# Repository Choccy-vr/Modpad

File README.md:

# Modpad
> An open-source, hot-swappable modular macro pad system with live browser-based key mapping.

Modpad combines hardware and software to create an adaptable modular macropad. Rather than locking users in a fixed, rigid layout, keyboard layout, or proprietary config software, Modpad allows users to magnetically hot-swap satellite modules into a main module and reconfigure key actions and layout all in real time.

Configurator URL: https://modpad.vercel.app/
Demo Video: https://youtu.be/VHo8qCPebk0

---
## Features
- **Dynamic Module Discovery:** Automatically identifies and polls attached satellite modules using i2c
- **Zero-Install Configurator:** Uses web serial to read active layouts, update bindings, and provide real-time input status all with a website.
- **Dynamic Remapping:** Keymaps are refreshed directly in the microcontroller's RAM; no need to restart every time.
- **Full HID & Consumer Control Support:** Emulates standard keyboard keystrokes, modifiers, and media controls (Volume, Play/Pause, Brightness).

## Modules
- **Macro:** The standard-sized macro pad. 6 completely remappable buttons.
- **Knobs:** 2 Rotary Encoders. Perfect for volume and brightness.
- More in the works

## Protocol
The web configurator and the main module communicate over USB serial (115200 baud) using newline-delimited JSON. Each message is a single JSON object ending in `\n`.

| Message | Direction | Description | Example |
|---|---|---|---|
| `get_layout` | Web -> Board | Requests the keymap of every module | `{"cmd":"get_layout"}` |
| `layout` | Board -> Web | Returns each module's keymap as a list of actions | `{"status":"layout","modules":{"Macro":[{"code":4,"mod":0,"consumer":false}, ...]}}` |
| `get_modules` | Web -> Board | Requests which modules are currently connected | `{"cmd":"get_modules"}` |
| `modules` | Board -> Web | Returns the connection state of each module | `{"status":"modules","modules":{"Macro":true,"Knobs":false}}` |
| `set_key` | Web -> Board | Rebinds one key or knob direction in RAM | `{"cmd":"set_key","module":"Macro","index":2,"code":4,"modifiers":0,"consumer":false}` |
| `ok` / `error` | Board -> Web | Reply to `set_key` | `{"status":"ok"}` / `{"status":"error","msg":"invalid_key_or_module"}` |
| `press` | Board -> Web | Sent whenever a button or knob is used | `{"status":"press","module":{"name":"Macro","index":2,"type":"button"}}` |
| `log` | Board -> Web | Debug message, so the serial stream stays pure JSON | `{"status":"log","msg":"..."}` |

### Fields
- `code`: HID keyboard usage ID, or a consumer usage ID when `consumer` is `true` (for example `0xE9` for Volume +).
- `modifiers` / `mod`: Modifier bitmask (`0x01` LCtrl, `0x02` LShift, `0x04` LAlt, `0x08` LGui, `0x10` RCtrl, `0x20` RShift, `0x40` RAlt, `0x80` RGui).
- `index`: Position in the module's keymap. It's the same index for `set_key` and `press`.

---

---
## Pictures
### Configurator

### Main Module
#### Schematic

#### PCB

#### PCB 3D model

#### CAD

### Macro Module
#### Schematic

#### PCB

#### PCB 3D model

#### CAD

### Knobs Module
#### Schematic

#### PCB

#### PCB 3D model

#### CAD

### Built

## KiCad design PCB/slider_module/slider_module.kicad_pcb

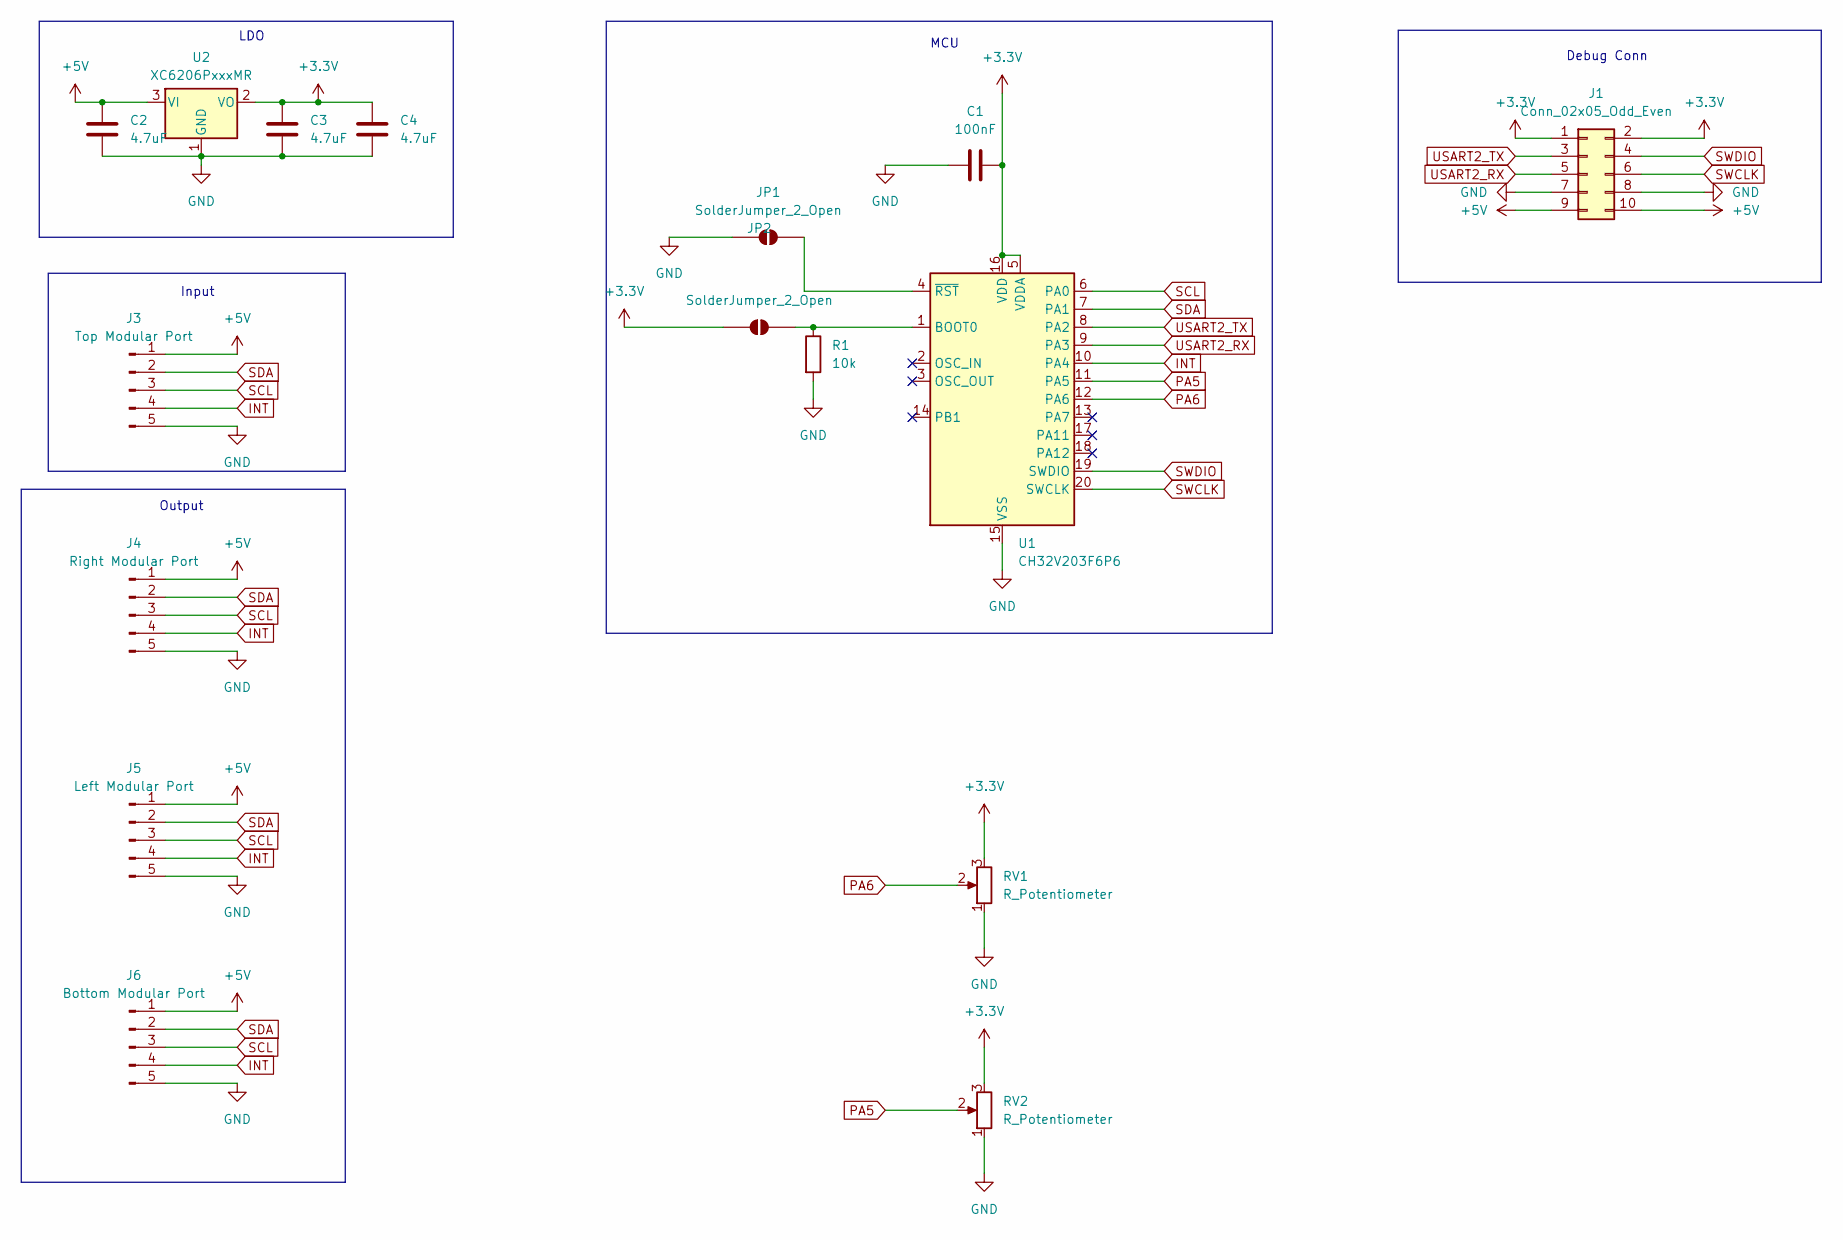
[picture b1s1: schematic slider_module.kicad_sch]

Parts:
C1: 100nF; C_0805_2012Metric
C2, C3, C4: 4.7uF; C_0805_2012Metric
J1: Conn_02x05_Odd_Even; PinSocket_2x05_P2.54mm_Vertical
J3: Top Modular Port; PinHeader_1x05_P2.54mm_Vertical
J4: Right Modular Port; PinHeader_1x05_P2.54mm_Vertical
J5: Left Modular Port; PinHeader_1x05_P2.54mm_Vertical
J6: Bottom Modular Port; PinHeader_1x05_P2.54mm_Vertical
JP1, JP2: SolderJumper_2_Open; SolderJumper-2_P1.3mm_Open_Pad1.0x1.5mm
R1: 10k; R_0805_2012Metric
RV1, RV2: R_Potentiometer; Potentiometer_Bourns_PTA4543_Single_Slide
U1: CH32V203F6P6; TSSOP-20_4.4x6.5mm_P0.65mm
U2: XC6206PxxxMR; SOT-23-3

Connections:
+3.3V: C1.2, C3.1, C4.1, J1.1, J1.2, JP2.1 (A), RV1.3, RV2.3, U1.5 (VDDA), U1.16 (VDD), U2.2 (VO)
+5V: C2.1, J1.9, J1.10, J3.1, J4.1, J5.1, J6.1, U2.3 (VI)
GND: C1.1, C2.2, C3.2, C4.2, J1.7, J1.8, J3.5, J4.5, J5.5, J6.5, JP1.1 (A), R1.2, RV1.1, RV2.1, U1.15 (VSS), U2.1 (GND)
INT: J3.4, J4.4, J5.4, J6.4, U1.10 (PA4)
unnamed: JP1.2 (B), U1.4 (~RST)
unnamed: JP2.2 (B), R1.1, U1.1 (BOOT0)
PA5: RV2.2, U1.11 (PA5)
PA6: RV1.2, U1.12 (PA6)
SCL: J3.3, J4.3, J5.3, J6.3, U1.6 (PA0)
SDA: J3.2, J4.2, J5.2, J6.2, U1.7 (PA1)
SWCLK: J1.6, U1.20 (SWCLK)
SWDIO: J1.4, U1.19 (SWDIO)
USART2_RX: J1.5, U1.9 (PA3)
USART2_TX: J1.3, U1.8 (PA2)

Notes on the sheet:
Debug Conn
Input
Output
LDO
MCU

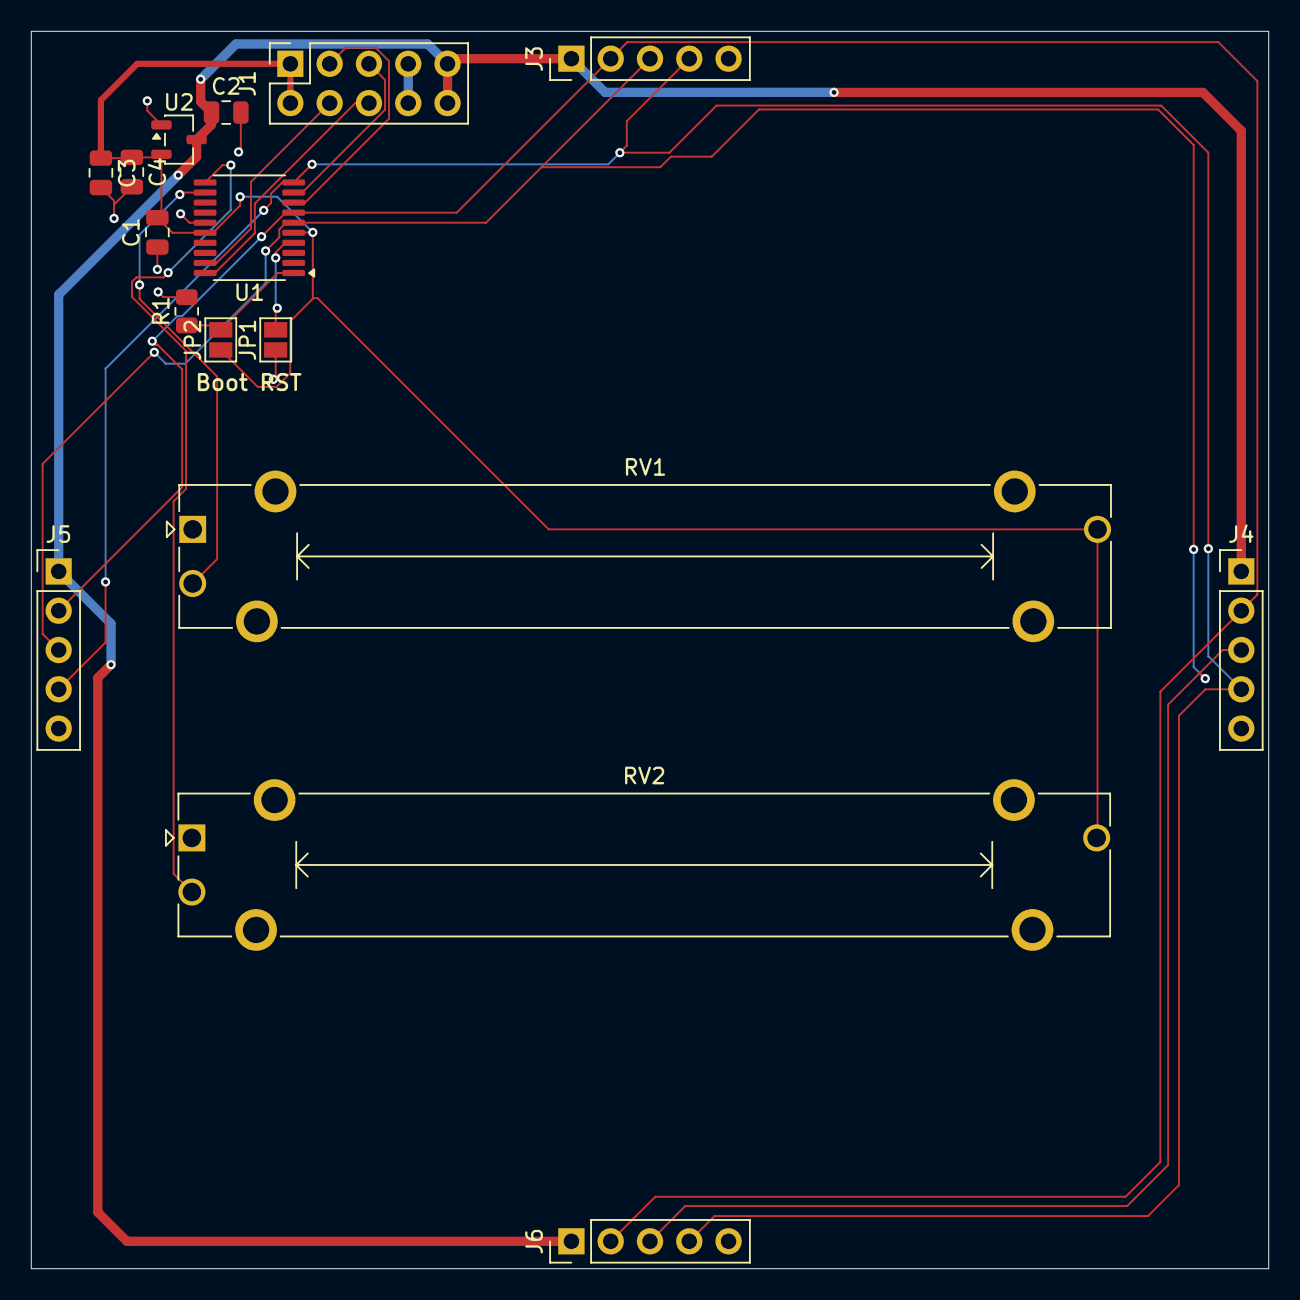
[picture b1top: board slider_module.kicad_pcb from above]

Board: 2 copper layers, 80.0 x 80.0 mm, 16 parts (0 on the bottom side), 14 nets.

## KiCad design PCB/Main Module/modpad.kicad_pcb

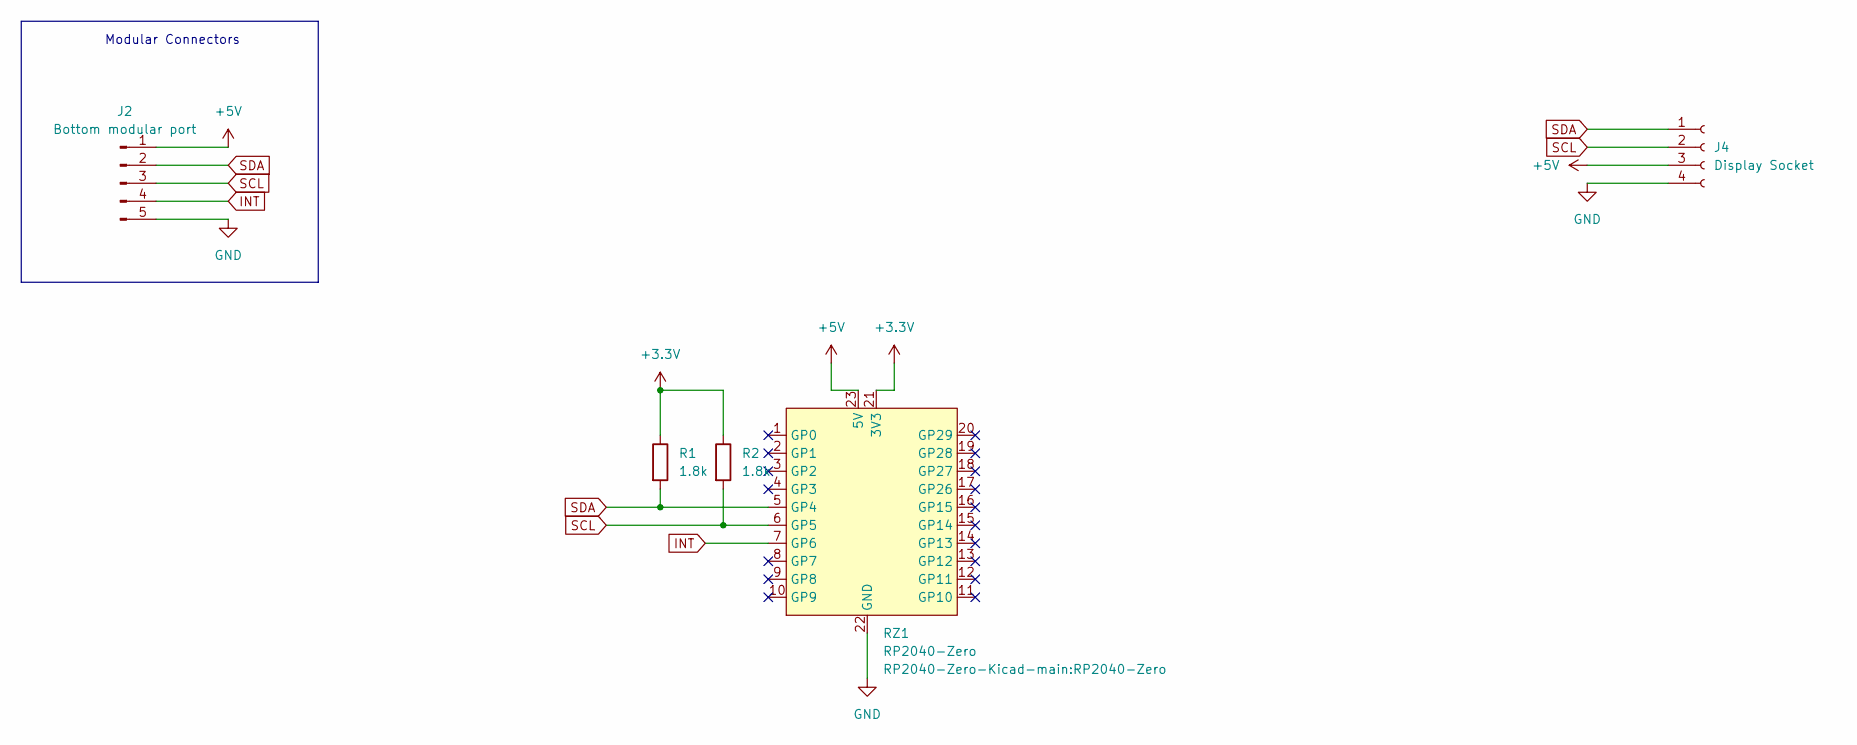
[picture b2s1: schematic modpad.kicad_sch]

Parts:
J2: Bottom modular port; PinHeader_1x05_P2.54mm_Vertical
J4: Display Socket; SSD1306-0.91-OLED-4pin-128x32
R1, R2: 1.8k; R_0805_2012Metric
RZ1: RP2040-Zero

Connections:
+3.3V: R1.1, R2.1, RZ1.21 (3V3)
+5V: J2.1, J4.3, RZ1.23 (5V)
GND: J2.5, J4.4, RZ1.22 (GND)
INT: J2.4, RZ1.7 (GP6)
SCL: J2.3, J4.2, R2.2, RZ1.6 (GP5)
SDA: J2.2, J4.1, R1.2, RZ1.5 (GP4)

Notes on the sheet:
Modular Connectors

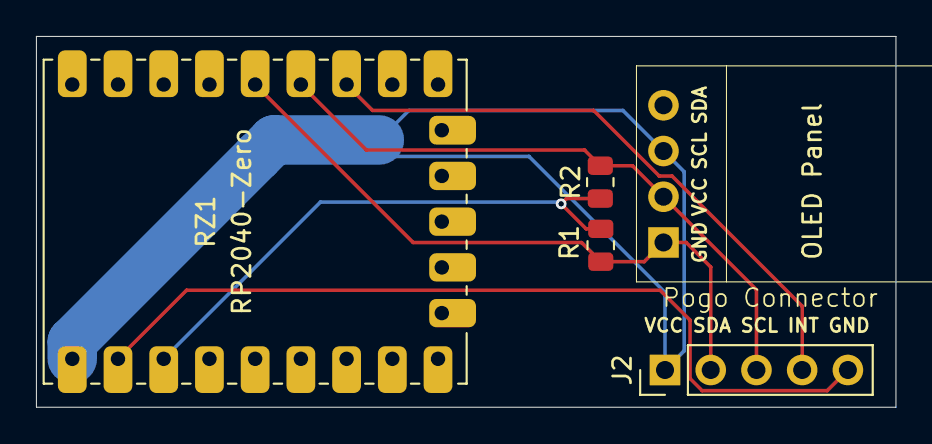
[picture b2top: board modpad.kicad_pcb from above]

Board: 2 copper layers, 47.7 x 20.6 mm, 5 parts (0 on the bottom side), 6 nets.
